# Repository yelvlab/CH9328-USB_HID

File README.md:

CH9328 PCB project

KiCAD 5.1.0

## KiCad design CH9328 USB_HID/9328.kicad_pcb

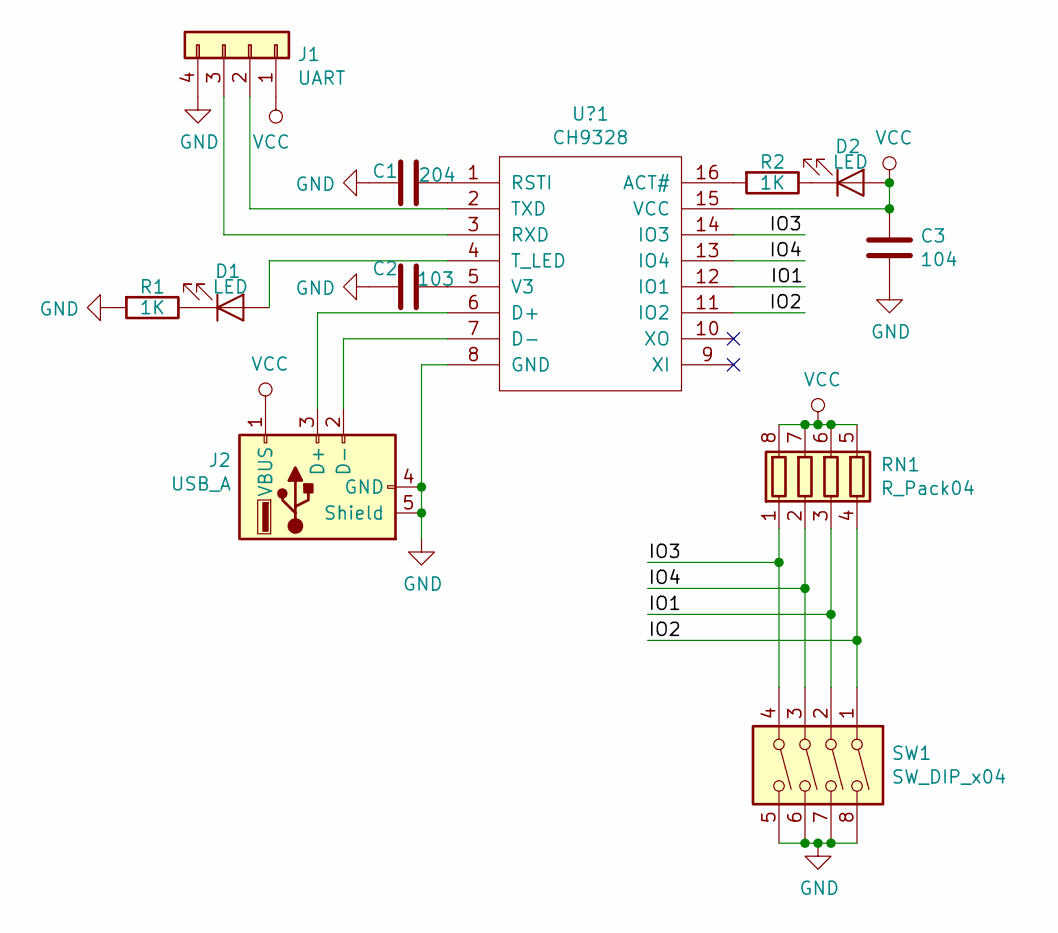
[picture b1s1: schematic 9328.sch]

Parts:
C1: 204; C_0603_HandSoldering
C2: 103; C_0603_HandSoldering
C3: 104; C_0603_HandSoldering
D1, D2: LED; LED_0603_HandSoldering
J1: UART; Pin_Header_Angled_1x04_Pitch2.54mm
J2: USB_A
R1, R2: 1K; R_0603_HandSoldering
RN1: R_Pack04; R_Cat16-4
SW1: SW_DIP_x04; SW_DIP_x4_W7.62mm_Slide
U?1: CH9328; SOP-16_4.4x10.4mm_Pitch1.27mm

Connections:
/IO1: RN1.3 (R3.1), SW1.2, U?1.12 (IO1)
/IO2: RN1.4 (R4.1), SW1.1, U?1.11 (IO2)
/IO3: RN1.1 (R1.1), SW1.4, U?1.14 (IO3)
/IO4: RN1.2 (R2.1), SW1.3, U?1.13 (IO4)
GND: C1.2, C2.2, C3.2, J1.4, J2.4 (GND), J2.5 (Shield), R1.2, SW1.5, SW1.6, SW1.7, SW1.8, U?1.8 (GND)
unnamed: C1.1, U?1.1 (RSTI)
unnamed: C2.1, U?1.5 (V3)
unnamed: D1.1 (K), R1.1
unnamed: D1.2 (A), U?1.4 (T_LED)
unnamed: D2.1 (K), R2.1
unnamed: J1.2, U?1.2 (TXD)
unnamed: J1.3, U?1.3 (RXD)
unnamed: J2.2 (D-), U?1.7 (D-)
unnamed: J2.3 (D+), U?1.6 (D+)
unnamed: R2.2, U?1.16 (ACT#)
VCC: C3.1, D2.2 (A), J1.1, J2.1 (VBUS), RN1.5 (R4.2), RN1.6 (R3.2), RN1.7 (R2.2), RN1.8 (R1.2), U?1.15 (VCC)

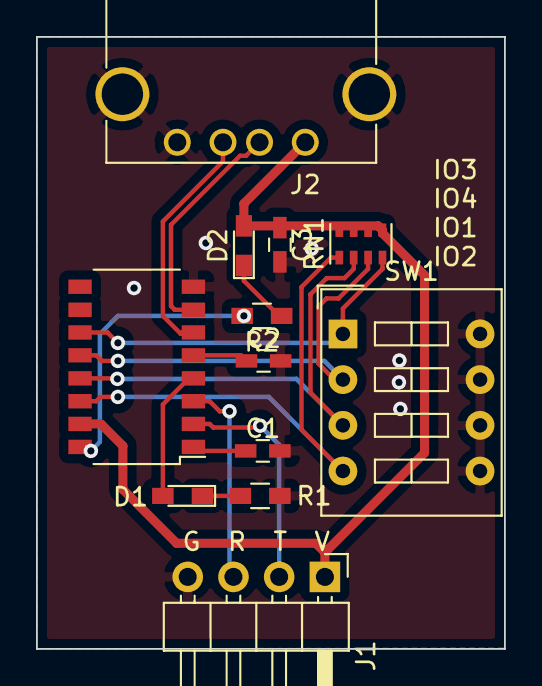
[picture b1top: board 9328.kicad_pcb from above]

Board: 2 copper layers, 26.0 x 34.0 mm, 12 parts (0 on the bottom side), 16 nets.

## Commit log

2019-04-21 add kicad project
2019-04-21 add readme
